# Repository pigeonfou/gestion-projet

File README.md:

# OddWorks — Gestion de projets

Application web PHP de gestion de projets, tâches, utilisateurs et cahiers des charges.

## Prérequis

- Linux (Ubuntu 22.04 / 24.04 / 26.04)
- PHP ≥ 8.1 + extensions `pdo_sqlite`, `mbstring`, `curl`, `xml` et `zip`
- Apache 2 + `libapache2-mod-php`
- Git

---

## Déploiement sur un Ubuntu fraîchement installé

Le dépôt contient un installateur interactif : `install/install_ubuntu.sh`.

### Installation recommandée

Depuis une session SSH sur un serveur Ubuntu 22.04, 24.04 ou 26.04 fraîchement installé :

```bash
sudo apt-get update
sudo apt-get install -y curl ca-certificates
curl -fsSL https://raw.githubusercontent.com/pigeonfou/gestion-projet/main/install/install_ubuntu.sh -o /tmp/projectflow-install.sh
sudo bash /tmp/projectflow-install.sh
```

Le menu permet de :

1. installer/déployer la branche `main` ;
2. vérifier une installation existante ;
3. consulter le journal d'installation.

Pour lancer directement l'installation sans menu :

```bash
sudo bash /tmp/projectflow-install.sh --install
```

### Ce que fait l'installateur

- vérifie qu'il s'agit d'Ubuntu ;
- installe Apache 2, PHP, SQLite, Git et les extensions PHP nécessaires ;
- clone ou met à jour `https://github.com/pigeonfou/gestion-projet.git` sur la branche `main` ;
- installe le projet dans `/var/www/html/gestion-projet` ;
- crée `/var/lib/projectflow` avec les droits nécessaires ;
- initialise la base SQLite si elle n'existe pas ;
- demande et confirme le mot de passe initial du compte `admin` ;
- applique les migrations du schéma et initialise les paramètres ;
- configure Apache pour autoriser le `.htaccess` du projet ;
- interdit l'accès HTTP au répertoire `install/` ;
- effectue un test HTTP local ;
- écrit le journal dans `/var/log/projectflow-install.log`.

La base SQLite reste hors du DocumentRoot :

```
/var/lib/projectflow/database.sqlite
```

L'installateur **ne réinitialise jamais une base existante**.

### Accès

Après installation :

```
http://IP_DU_SERVEUR/gestion-projet/
```

Le compte initial est :

```
identifiant : admin
```

Le mot de passe est celui saisi et confirmé pendant l’installation (12 caractères minimum). Aucun mot de passe de démonstration n’est créé par l’installateur.

### Pare-feu (optionnel)

Si `ufw` est installé :

```bash
sudo ufw allow OpenSSH
sudo ufw allow 'Apache Full'
sudo ufw enable
```

### Installation manuelle

La procédure manuelle reste possible si nécessaire :

```bash
sudo apt update && sudo apt upgrade -y
sudo apt install -y apache2 php php-sqlite3 php-mbstring php-curl php-xml php-zip libapache2-mod-php git
cd /var/www/html
sudo git clone --branch main https://github.com/pigeonfou/gestion-projet.git
sudo chown -R www-data:www-data gestion-projet
sudo install -d -o www-data -g www-data -m 750 /var/lib/projectflow
cd /var/www/html/gestion-projet
sudo -u www-data php install/init_database.php
```

Après l'initialisation manuelle, une première exécution de l'application applique les migrations du schéma. L'installateur automatique effectue cette étape immédiatement et vérifie également Apache et SQLite.

---

## Mise à jour et rollback

Le projet fournit deux scripts d'exploitation pour mettre à jour le serveur ou revenir à une version précédente :

- `scripts/update_gestion_projet.sh` : mise à jour vers une branche Git ;
- `scripts/rollback_gestion_projet.sh` : retour interactif vers l'un des 10 derniers commits de la branche.

Les deux scripts sont prévus pour être exécutés sur le serveur avec les droits administrateur.

### Mise à jour

Pour mettre à jour la branche `main` :

```bash
cd /var/www/html/gestion-projet
sudo bash scripts/update_gestion_projet.sh
```

La branche `main` est utilisée par défaut. Une autre branche peut être indiquée :

```bash
sudo bash scripts/update_gestion_projet.sh Stock
```

Le script :

1. sauvegarde la base SQLite dans `/var/backups/gestion-projet/` ;
2. récupère les modifications depuis GitHub ;
3. vérifie que la branche demandée existe ;
4. bascule sur cette branche ;
5. met à jour le code avec `git reset --hard origin/<branche>` ;
6. vérifie la syntaxe de tous les fichiers PHP ;
7. vérifie la configuration Apache puis recharge Apache.

Le script affiche à la fin le commit effectivement installé et le chemin de la sauvegarde de la base.

> **Important :** les éventuelles modifications locales du code sont écrasées par la mise à jour. Le script sauvegarde la base avant l'opération, mais pas les modifications locales du dépôt.

### Rollback

Pour revenir à une version précédente de `main` :

```bash
cd /var/www/html/gestion-projet
sudo bash scripts/rollback_gestion_projet.sh
```

Une autre branche peut également être indiquée :

```bash
sudo bash scripts/rollback_gestion_projet.sh Stock
```

Le script :

1. vérifie l'état du dépôt et refuse l'opération en présence de modifications locales ;
2. récupère la branche depuis GitHub ;
3. affiche les 10 derniers commits disponibles ;
4. demande de sélectionner la version à restaurer ;
5. demande une confirmation explicite en saisissant `ROLLBACK` ;
6. sauvegarde la base SQLite avant l'opération ;
7. crée une branche locale de sauvegarde du commit actuellement installé ;
8. revient au commit sélectionné, vérifie PHP et recharge Apache.

Le rollback **ne restaure pas la base de données**. Une sauvegarde de la base est créée avant le rollback dans `/var/backups/gestion-projet/`, mais elle n'est pas automatiquement réinjectée. Cette précaution évite qu'un retour du code ne détruise des données créées par une version plus récente.

### Sauvegardes de la base

Les scripts créent leurs sauvegardes dans :

```text
/var/backups/gestion-projet/
```

Il est recommandé de conserver ces sauvegardes et de prévoir une stratégie de sauvegarde externe régulière pour la base SQLite de production.

---

## Configuration du chemin de base

Le fichier `config/config.php` contient :

```php
define('BASE_PATH', '/gestion-projet');
// DB_PATH peut être surchargé par la variable d'environnement PROJECTFLOW_DB_PATH.
```

- Laissez `/gestion-projet` si le projet est dans un sous-dossier (recommandé).
- Mettez `''` (chaîne vide) si vous placez le projet directement à la racine du DocumentRoot.

---

## Structure

```
gestion-projet/
├── admin/               # Gestion des utilisateurs
├── assets/              # CSS & JS
├── config/              # Configuration (BASE_PATH + DB)
├── includes/            # Auth, header, footer
├── install/             # Script d’initialisation de la base
├── index.php
├── login.php
├── projets.php
├── projet.php
├── tache.php
├── cahier.php
└── README.md
```

## Sécurité

- Mots de passe hashés (`password_hash` / `password_verify`)
- Requêtes préparées PDO
- Échappement HTML (`htmlspecialchars`)
- Vérification des droits à chaque action sensible
- Protection CSRF des mutations
- Suppression des actions destructives en GET
- Sessions sécurisées et régénérées à la connexion
- Base SQLite hors du DocumentRoot

## Indépendance de l'application

OddWorks est installé et exploité sans OneForAll. Le dépôt fournit son propre installateur Ubuntu, ses scripts de maintenance et ses tests. La publication externe et les tunnels réseau ne sont pas gérés par OddWorks.

**Attention sur un serveur déjà occupé :** l'installateur historique installe Apache et exécute `apt-get upgrade`, puis redémarre Apache. Ne pas l'exécuter sur le serveur actuel sans adapter l'installation à Nginx/PHP-FPM et vérifier les ports.

La branche `extraction-oddworks-autonome` est une branche de préparation : aucune installation en production ne doit être déclenchée depuis cette branche.

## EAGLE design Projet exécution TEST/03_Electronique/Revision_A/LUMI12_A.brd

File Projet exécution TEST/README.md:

# Projet exécution TEST - LUMI-12

Exercice manuel OddWorks : deux témoins lumineux 12 V et un outil PC C++ de recette.
Tout est fictif : personnes, fournisseur, visas, certificats, SDS, datasheets,
mesures et identifiants Git. Aucun achat, message ni essai matériel réel.

## Commencer

1. Lire `00_Parcours/00_GUIDE_EXECUTION_LUMI12.pdf` (18 épisodes).
2. Créer soi-même le projet `RECETTE-MANUELLE-LUMI12-2026` dans OddWorks.
3. Utiliser les pièces au fil de leur réception dans le récit ; garder les indices.
4. Ouvrir `99_Correction/99_CORRIGE_LUMI12.pdf` seulement après l’exercice.

Le ZIP contient le même dossier, sans le ZIP lui-même. Les tableaux CSV sont des
fiches de saisie, pas des imports automatiques dans OddWorks.

## Histoire et points à vérifier

- Dates métier simulées du 2 au 18 novembre 2026 ; exécution possible en une séance.
- CDC R0.1 refusé, puis R1.0 accepté : ne pas confondre refus documentaire et NO GO.
- 3 S.F. et 8 S.T. couvrant Matériel, Composant, Prestataire, Logiciel, 3D et PCB.
- Quantités/prix par prototype, quantité CDC de 2 : 40 € HT initialement, 43,80 € après
  surcoût PCB et substitution LED, pour un budget global de 60 € HT.
- Hiérarchie parent-enfant indépendante du type de référence S.T.x.x.
- Retard fournisseur et livraison finale +5 jours calendaires / +3 jours ouvrés.
- Mauvais dimensionnement de résistances en A, outil A incomplet, non-conformité,
  DM01, résistances 1 kΩ et outil B, contre-essais et livraison.
- ISO 14001 expiré puis renouvelé ; SDS distincte des certificats et des attestations
  RoHS/REACH. La conformité inconnue n’est pas inventée.
- Lot fictif en quarantaine puis libéré, pas de double entrée de stock.
- Fin du processus à 100 % avec TRL 4 et cible 7 non atteinte.

## Particularités de mise en œuvre

Un seul compte : les personnages représentent des validations métier narrées dans
les documents, pas des utilisateurs à créer ou à incarner. Aucune notification réelle.
Attendre le message de sauvegarde avant de naviguer. Si un clic est ambigu, utiliser
Tab jusqu’au bouton puis Entrée, sans modifier le DOM ni contourner une validation.

Nextcloud peut être absent : garder alors les preuves localement, saisir leurs
références et déclarer le dépôt documentaire NON EXÉCUTÉ. Ne pas inventer de lien.
La production avec ordre d’assemblage nécessite une instruction Nextcloud : ce
sous-parcours s’arrête si aucune instruction n’est disponible. Il n’est pas requis
pour le parcours principal, qui reste une recette documentaire du processus.

Les dates serveur sont réelles et inchangées. Le badge de retard dépend de l’horloge
réelle ; les retards de ce récit sont vérifiés par les dates métier et les notes.
Les quantités des tâches achat générées doivent être vérifiées : ne pas supposer
une multiplication implicite par la quantité globale du CDC.

## Livrables techniques et portée

- `03_Electronique/Revision_A` et `Revision_B` : paires EAGLE XML .sch/.brd avec
  bibliothèque synthétique embarquée, pas de fichiers renommés depuis un autre format.
- `04_Mecanique` : STEP fond, couvercle, carte nue de référence, assemblage ; aperçu SVG.
- `05_Logiciel` : source C++ A/B et SHA fictifs de 40 caractères, non résolubles sur GitHub.
- `02_Fournisseurs` : 4 datasheets, SDS en 16 rubriques et 3 attestations ISO fictives.
- CDC, retours de validation, réunions, retard, accord, DM01, rapports d’essais et PV.

Les fichiers XML et les netlists sont contrôlés ; les STEP sont réimportés et leurs
solides/volumes vérifiés ; les deux programmes sont compilés et leurs décisions testées.
Aucun import dans un éditeur EAGLE/Fusion, ERC/DRC natif ou qualification de fabrication
n’a été réalisé. Le PCB et le boîtier ne sont pas à fabriquer en l’état.
Les documents de sécurité/certification sont impropres à tout usage réglementaire réel.

## Reproduction

`python3 generer_dossier.py` avec ReportLab, pypdf, CadQuery/OpenCascade et g++.
Les rendus PNG de contrôle ne font pas partie du livrable. Les sources, le manifeste
SHA-256 et le rapport de validation sont inclus pour permettre une vérification.

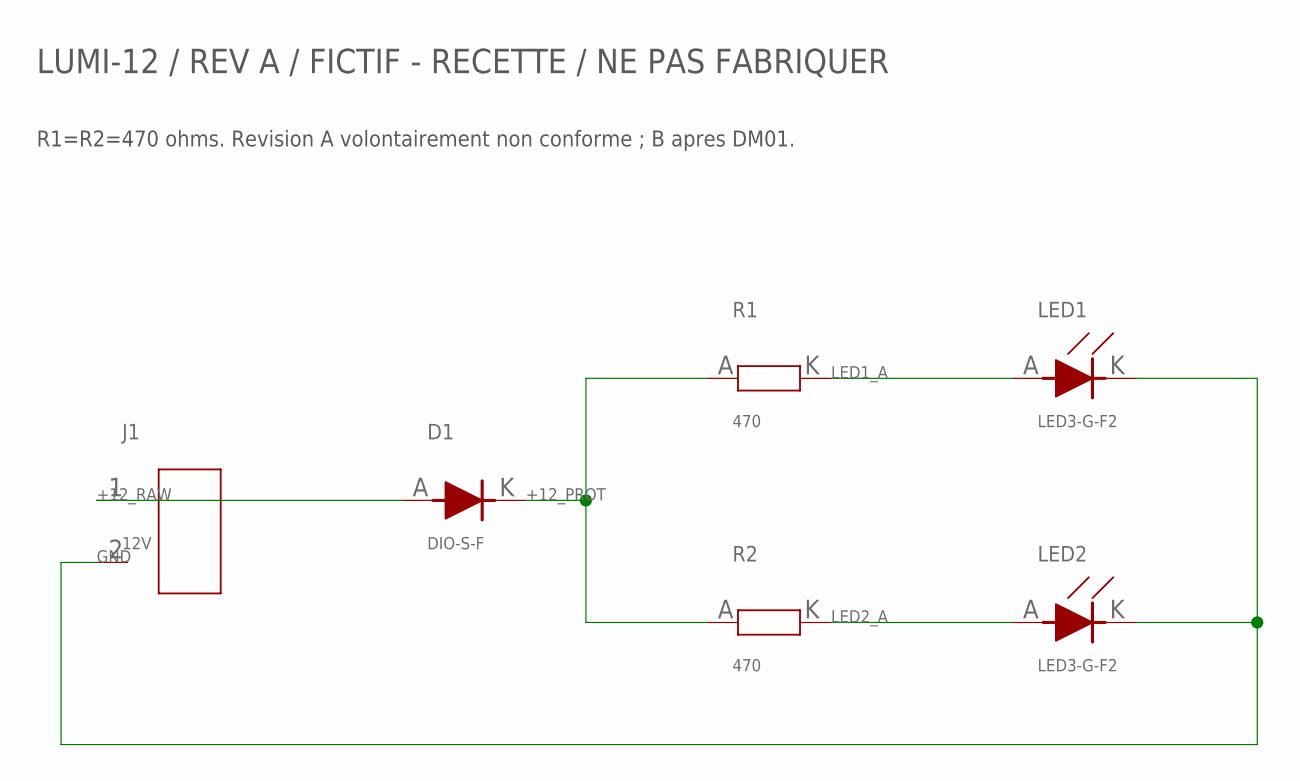
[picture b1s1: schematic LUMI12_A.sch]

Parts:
D1: DIO-S-F; AXIAL
J1: 12V; BORNIER5
LED1, LED2: LED3-G-F2; LED3
R1, R2: 470; AXIAL

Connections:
+12_PROT: D1.K, R1.A (1), R2.A (1)
+12_RAW: D1.A, J1.1
GND: J1.2, LED1.K, LED2.K
LED1_A: LED1.A, R1.K (2)
LED2_A: LED2.A, R2.K (2)

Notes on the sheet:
LUMI-12 / REV A / FICTIF - RECETTE / NE PAS FABRIQUER
R1=R2=470 ohms. Revision A volontairement non conforme ; B apres DM01.

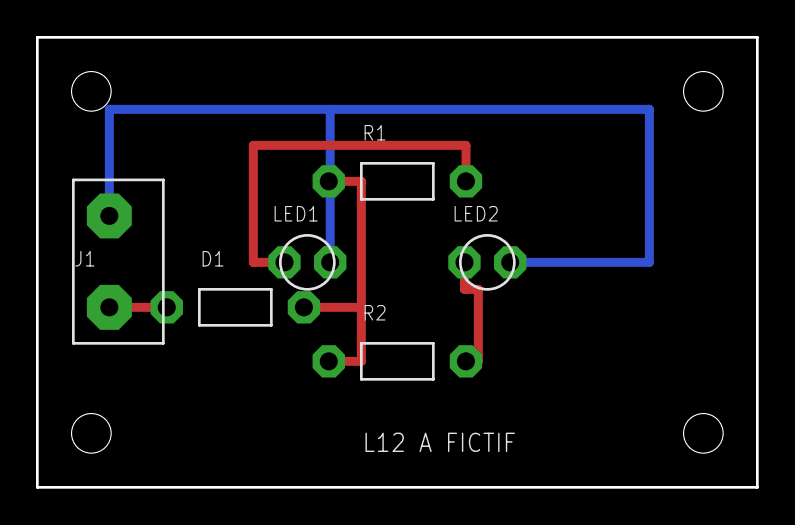
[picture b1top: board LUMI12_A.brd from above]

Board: 2 copper layers, 40.0 x 25.0 mm, 6 parts (0 on the bottom side), 5 nets.
